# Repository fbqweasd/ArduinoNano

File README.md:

# Arduino Nano - UKC

kicad를 사용하여 아두이노 NANO회로 설계

__사용프로그램 : kicad__

__MCU : ATmega328__

## 회로도

구글에서 여러가지 문서를 참고하여 설계를 하였습니다.

ATmega328로 설계하는 것이 처음이고 아두이노 부트로더를 올려 사용하려고 해서 사용하지 않는 핀과 제대로 이해를 하지 못한 부분이 있습니다.

## Artwork

개발 보드를 만들어 본 적이 없어서 상당히 더럽고 지저분하게 만들어져있습니다.

별로 어렵지 않고 간단한 회로인데 만드는 과정에서 많이 어렵게 만들어서 저의 경험이 많이 부족한 것을 느끼고 있네요...

## 후기

 공부용으로는 몇번 회로 설계를 한적이 있지만 Artwork는 많이 한적이 없었는데 이번에 Artwork을 하면서 저의 경험이 많이 부족하다는 것을 느꼈습니다. 

 footprint를 이상한 것을 쓰고 수치계산을 하지 못해서 처음 예상한 크기와 다른 모습으로 결과물이 나와서 많이 아쉬웠습니다. 그래서 더 많은 회로 설계를 해보면서 다음 번엔 더 좋은 결과물이 나오길 기대합니다.

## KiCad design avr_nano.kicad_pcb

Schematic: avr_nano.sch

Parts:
0.1uF1: C; C_0402_1005Metric
16Mhz1: Crystal; Crystal_C26-LF_D2.1mm_L6.5mm_Horizontal
C1: 0.1uF; C_0603_1608Metric
C2, C3: CP1; CP_EIA-2012-12_Kemet-R_Pad1.30x1.05mm_HandSolder
D1: LED; LED_D1.8mm_W1.8mm_H2.4mm_Horizontal_O1.27mm_Z8.2mm
J2: JP; Hirose_DF63-6P-3.96DSA_1x06_P3.96mm_Horizontal
J3: OUTPUT1; PhoenixContact_MCV_1,5_12-G-5.08_1x12_P5.08mm_Vertical
J4: OUTPUT2; PhoenixContact_MCV_1,5_12-G-5.08_1x12_P5.08mm_Vertical
R1: R; R_LDR_5.0x4.1mm_P3mm_Vertical
R2: 330R; R_LDR_5.0x4.1mm_P3mm_Vertical
SW1: SW_DIP_x01; SW_DIP_x1_W7.62mm_Slide
U1: ATmega328-AU; TQFP-32_7x7mm_P0.8mm

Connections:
A0: J4.8, U1.23 (PC0)
A1: J4.7, U1.24 (PC1)
A2: J4.6, U1.25 (PC2)
A3: J4.5, U1.26 (PC3)
A6: U1.19 (ADC6)
A7: U1.22 (ADC7)
D2: J3.5, U1.32 (PD2)
D3: J3.6, U1.1 (PD3)
D4: J3.7, U1.2 (PD4)
D5: J3.8, U1.9 (PD5)
D6: J3.9, U1.10 (PD6)
D7: J3.10, U1.11 (PD7)
D8: J3.11, U1.12 (PB0)
D9: J3.12, U1.13 (PB1)
D10: J4.12, U1.14 (PB2)
DTR: C1.1, J2.6
GND: 0.1uF1.2, C2.2, C3.2, D1.1, J2.1, J2.2, J3.4, J4.2, SW1.1, U1.3 (GND), U1.5 (GND), U1.21 (GND)
MISO: J4.10, U1.16 (PB4)
MOSI: J4.11, U1.15 (PB3)
unnamed: 0.1uF1.1, U1.20 (AREF)
unnamed: C1.2, R2.2, SW1.2, U1.29 (~RESET~/PC6)
unnamed: D1.2, R1.2
RAW: J4.1
RESET: J3.3, J4.3
RX1: J2.4, J3.2, U1.30 (PD0)
SCK: J4.9, R1.1, U1.17 (PB5)
TX0: J2.5, J3.1, U1.31 (PD1)
XTAL1: 16Mhz1.1, C2.1, U1.7 (XTAL1/PB6)
XTAL2: 16Mhz1.2, C3.1, U1.8 (XTAL2/PB7)

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
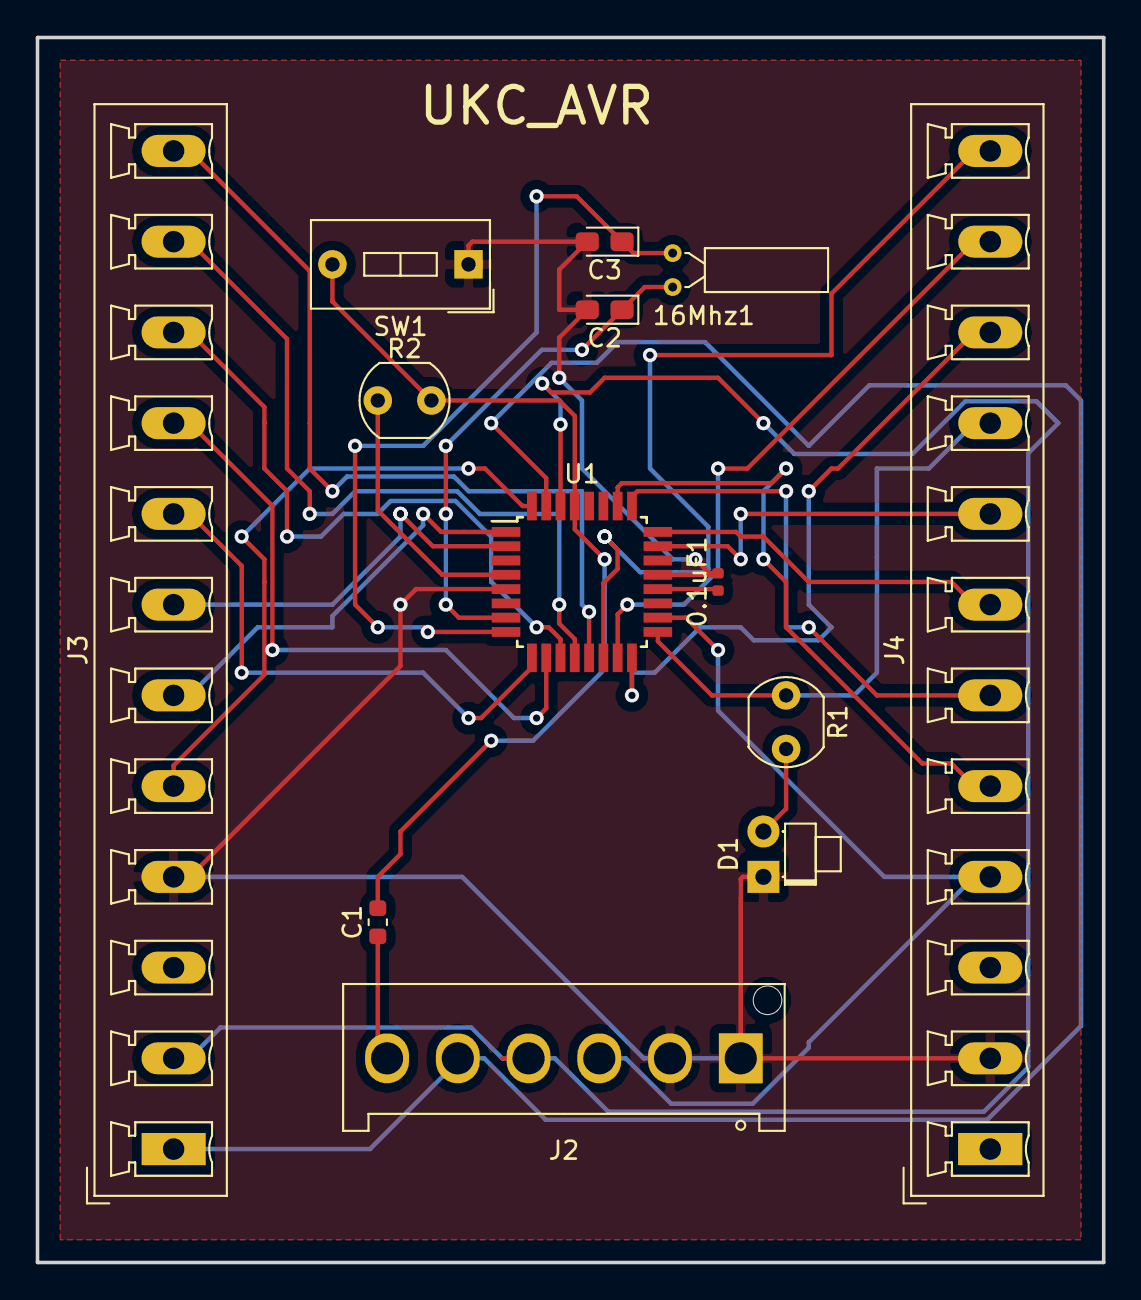
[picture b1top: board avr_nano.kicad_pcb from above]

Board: 2 copper layers, 59.7 x 68.6 mm, 13 parts (0 on the bottom side), 27 nets.

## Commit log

2018-11-17 UKC_nano
2018-11-17 README update
